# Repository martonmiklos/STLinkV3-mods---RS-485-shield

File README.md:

### STLinkV3 mods - RS-485 adapter board

I needed to debug some RS-485 equipped STM32 based gear and I wanted to reduce the burden on my desk by using the STLink's VCP port for RS-485.

Uses ISL83488IBZ-T full duplex transceiver, with pop options it is possible to populate it with RS-422 mode.

Drawn in Kicad 8.0

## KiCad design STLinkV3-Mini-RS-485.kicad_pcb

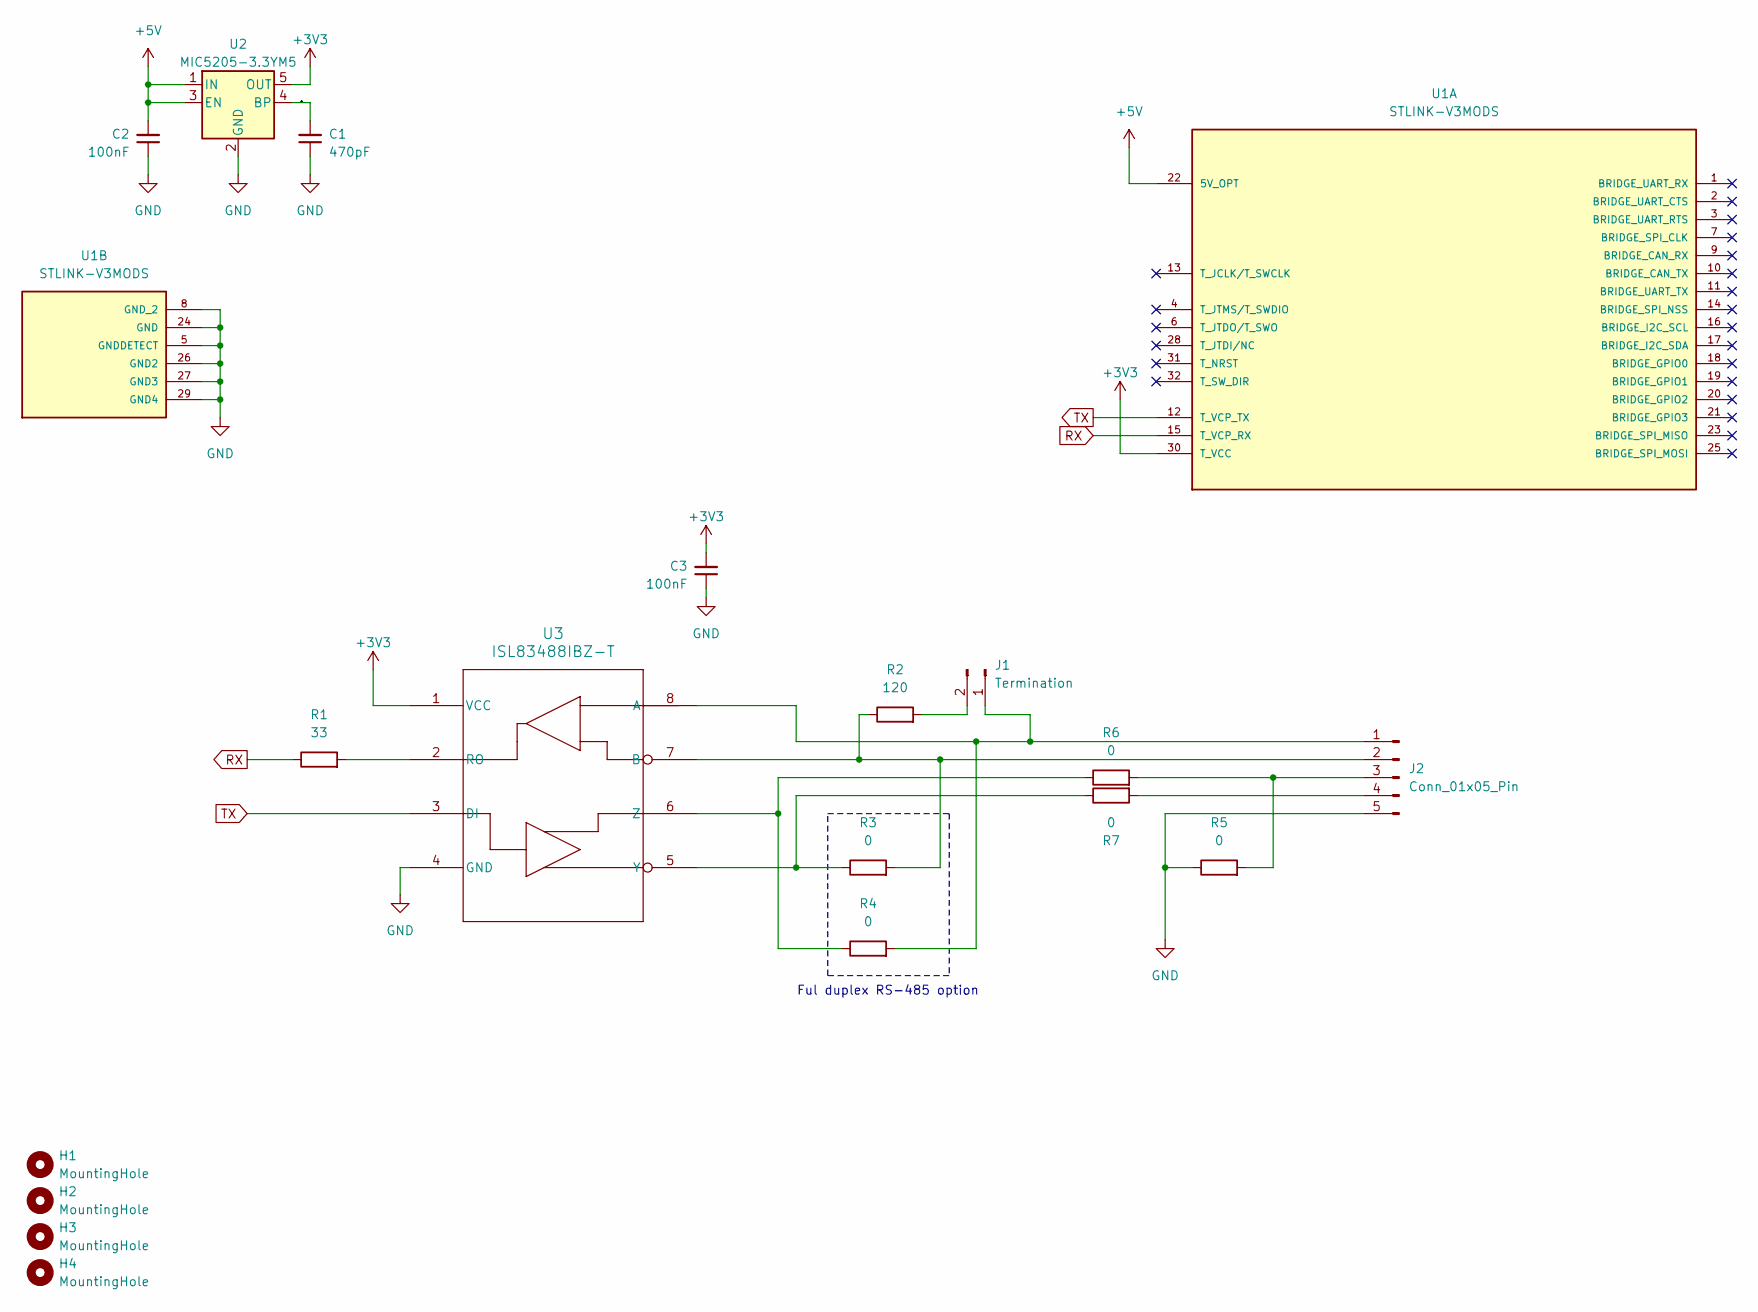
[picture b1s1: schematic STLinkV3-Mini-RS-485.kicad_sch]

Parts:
C1: 470pF; C_0603_1608Metric
C2, C3: 100nF; C_0603_1608Metric
H1, H2, H3, H4: MountingHole; MountingHole_3.2mm_M3
J1: Termination; PinHeader_1x02_P2.54mm_Vertical
J2: Conn_01x05_Pin; PhoenixContact_MC_1,5_5-G-3.81_1x05_P3.81mm_Horizontal
R1: 33; R_0603_1608Metric
R2: 120; R_1206_3216Metric
R3, R4, R5, R6, R7: 0; R_0603_1608Metric
U1: STLINK-V3MODS; MODULE_STLINK-V3MODS; PARTREV 1
U2: MIC5205-3.3YM5; SOT-23-5
U3: ISL83488IBZ-T; SOIC_488IBZ-T_REN

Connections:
+3V3: C3.2, U1.30 (T_VCC), U2.5 (OUT), U3.1 (VCC)
+5V: C2.2, U1.22 (5V_OPT), U2.1 (IN), U2.3 (EN)
/MIC5205_BYPASS: C1.2, U2.4 (BP)
GND: C1.1, C2.1, C3.1, J2.5, R5.1, U1.5 (GNDDETECT), U1.8 (GND_2), U1.24 (GND), U1.26 (GND2), U1.27 (GND3), U1.29 (GND4), U2.2 (GND), U3.4 (GND)
unnamed: J1.1, J2.1, R4.2, U3.8 (A)
unnamed: J1.2, R2.2
unnamed: J2.2, R2.1, R3.2, U3.7 (B)
unnamed: J2.3, R5.2, R6.2
unnamed: J2.4, R7.2
unnamed: R1.2, U3.2 (RO)
unnamed: R3.1, R7.1, U3.5 (Y)
unnamed: R4.1, R6.1, U3.6 (Z)
RX: R1.1, U1.15 (T_VCP_RX)
TX: U1.12 (T_VCP_TX), U3.3 (DI)

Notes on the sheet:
Ful duplex RS-485 option

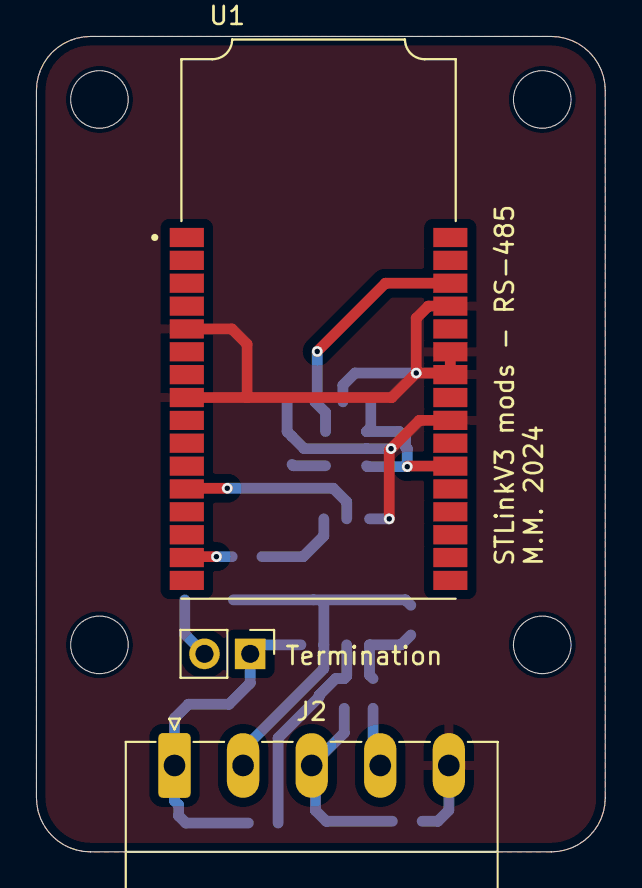
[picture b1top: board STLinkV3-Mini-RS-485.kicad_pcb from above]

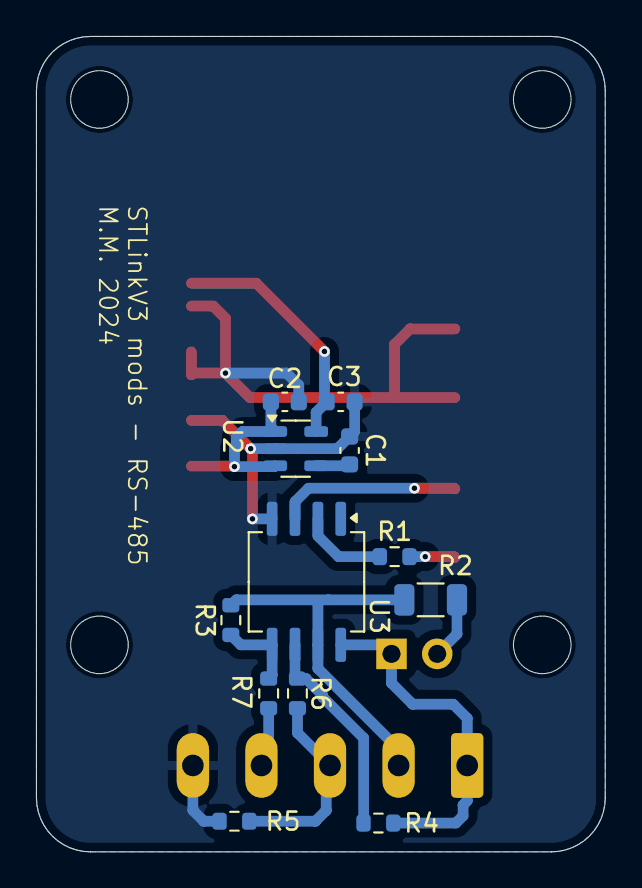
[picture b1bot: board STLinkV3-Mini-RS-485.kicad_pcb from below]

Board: 2 copper layers, 31.6 x 45.3 mm, 19 parts (12 on the bottom side), 14 nets.

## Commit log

2024-10-23 Repo init
